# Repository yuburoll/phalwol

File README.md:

# phalwol
Row staggered 60% keyboard with reversible PCB, inspired by [Hatsukey70](https://scrapbox.io/Hatsukey/)

Hatsuki means August in Japanese, and phalwol means August in Korean. This keyboard layout is an hommage to Hatsukey70, so I want to credit the original design by name.

This keyboard has additional Y/H/B keys which positioned between keyboards, and auxilary row at left outside. You may put the keycaps from numpad.

This keyboard has hotswap-only PCB.

phalwol can change layout to followings:

- Split left shift, to ISO shaped one.(2.25u to 1.25u/1u)

- Split right shift, to HHKB inspired shape.(2.75u to 1.75u/1u)

- Split outside thumb keys(2u to 1u/1u)

- Split backspace(2u to 1u/1u)

- Can use stepped caps lock

## Preparation

- 2x pro micro form factor dev board

- 2x phalwol PCB Boards, provided from the repo

- 1x printed case sets, 2 parts total, provided from the repo (for thicker case, use "buffed")

- 1x 1.5-1.6T keyboard plate sets, 2 parts total, provided from the repo

- 80x diodes, normally 1N4148

- 84x Kailh hotswap sockets (or compatibles)

- 16x M2x6 screws, flathead

- 2x PJ320A 1/8(3.5mm) TRRS connector (MJ-4PP-9 in other name)

- 2x 4x4x1.5mm surface mount tact switches (optional, for dev boards without reset button)

- 1x 1/8(3.5mm) TRRS cable

- 1-6x PCB Mounted 2u Keyboard Stabilizers, normally 6

- 73-78x MX Keyswitches, normally 73

- 8x 10mm bumpon stickers

- A set of Keycaps, Full-size layout, ANSI preferred.

## Differences between case variations

|Original|Buffed|Frame|
|:---:|:---:|:---:|
||||

(Frame case are lightest option for 3d print, but it is very brittle)

## Build Guides and Miscellaneous

[phalwol Build Guide](docs/buildGuide.md)

there's some notices before the build:

- You may solder all hotswaps before soldering the dev board.

- Assemble dev board with 2.5mm height pin headers on back side, assume that components side are faced up.

- Jump every jumpers on front side.

[Additional Tenting Stand](https://github.com/yuburoll/yubuGadgets/tree/main/phalilwolTentingStand)

Also take a look at the sibling, [ilwol](https://github.com/yuburoll/ilwol).

## Licenses

All codes are in MIT License.

Markdown documents and photos in docs/images folder are copyrighted, all rights reserved.

The case and layout design of Phalwol is licensed under CC BY-NC-SA 4.0 (Attribution-NonCommercial-ShareAlike) by default, with an additional limited permission for commercial use under the following conditions:

- You are an individual, not acting on behalf of any company or organization.
  
- Your revenue from a single batch of sales does not exceed $2,000.
  
- Your sales are occasional and limited in scope, not ongoing or continuous.

If you want to ask any, please contact the authors.

- me: yuburoll@gmail.com

- Murasaki, the author of original layout Hatsukey70: https://scrapbox.io/Hatsukey/%E4%BD%9C%E8%80%85%E9%80%A3%E7%B5%A1%E5%85%88

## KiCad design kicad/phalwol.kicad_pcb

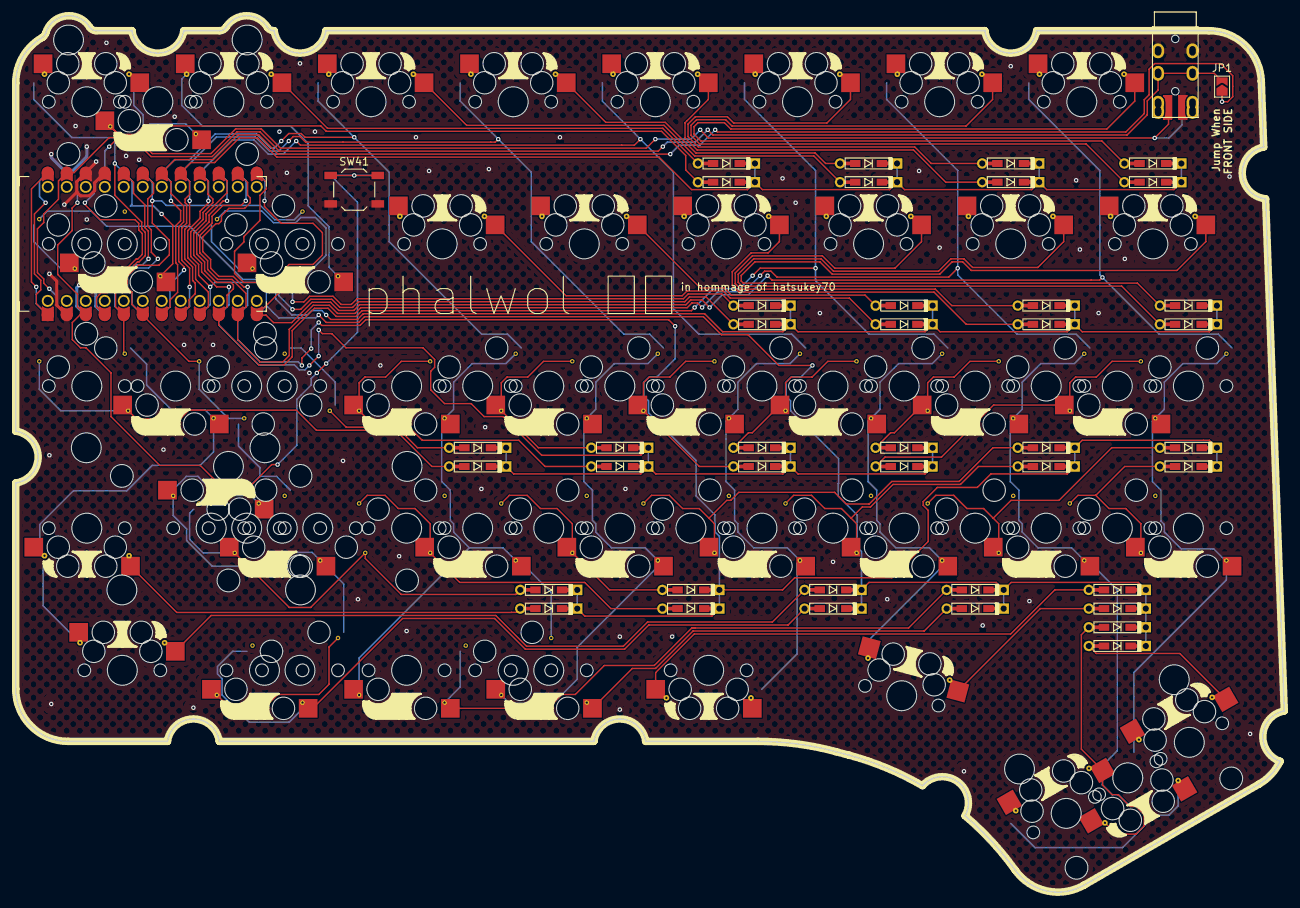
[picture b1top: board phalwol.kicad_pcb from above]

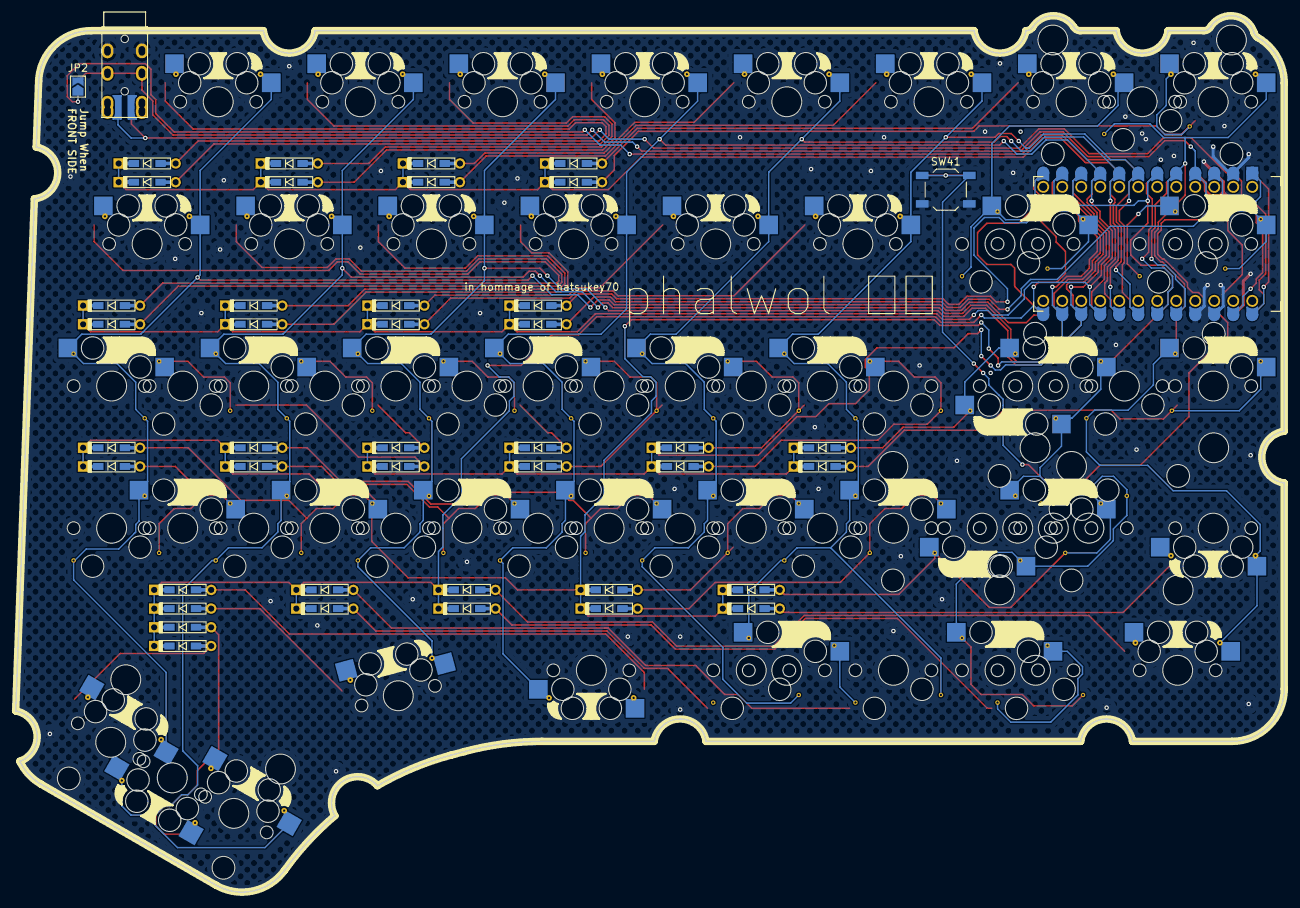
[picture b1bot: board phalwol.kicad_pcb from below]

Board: 2 copper layers, 169.6 x 117.1 mm, 108 parts (23 on the bottom side), 58 nets.

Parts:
D1, D2, D3, D4, D5, D6, D7, D8, D9, D10, D11, D12, D13, D14, D15, D16, D17, D18, D19, D20, D21, D22, D23, D24, D25, D26, D27, D28, D29, D30, D31, D32, D33, D34, D35, D36, D37, D38, D39, D40: D; Diode_TH_SMD_REVERSIBLE
J1: AudioJack4; TRRS-PJ-320A-ReversiblePad
JP1, JP2: SolderJumper_2_Open; SolderJumper-2_P1.3mm_Open_TrianglePad1.0x1.5mm
SW1, SW9, SW9#2, SW10, SW10#2, SW17, SW17#2, SW18, SW19, SW19#2, SW20, SW20#2, SW21, SW21#2, SW22, SW22#2, SW23, SW23#2, SW24, SW24#2, SW26, SW26#2, SW26#3, SW26#4, SW27, SW27#2, SW28, SW28#2, SW29, SW29#2, SW30, SW30#2, SW31, SW31#2, SW32, SW32#2, SW34, SW34#2, SW35, SW35#2, SW36: SW_Push; MX_HotswapOneside_Via_Guided
SW1#2, SW2, SW3, SW4, SW5, SW6, SW7, SW8, SW11, SW12, SW13, SW14, SW15, SW16, SW25, SW33, SW37, SW38, SW39, SW39#2, SW40: SW_Push; MX_Hotswap_FootprintPropertyFix_Guided
SW41, SW41#2: SW_Push; SW_SPST_TL3342
U1: ProMicro; ProMicro_ReveribleThru_ComponentUp_OuterPad

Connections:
COL1: SW1.1, SW1#2.1, SW9.1, SW9#2.1, SW17.1, SW17#2.1, SW25.1, SW33.1, U1.20 (F4/A3)
COL2: SW2.1, SW10.1, SW10#2.1, SW18.1, SW26.1, SW26#2.1, SW26#3.1, SW26#4.1, SW34.2, SW34#2.1, U1.19 (F5/A2)
COL3: SW3.1, SW11.1, SW19.1, SW19#2.1, SW27.1, SW27#2.1, SW35.2, SW35#2.1, U1.18 (F6/A1)
COL4: SW4.1, SW12.1, SW20.1, SW20#2.1, SW28.1, SW28#2.1, SW36.2, U1.17 (F7/A0)
COL5: SW5.1, SW13.1, SW21.1, SW21#2.1, SW29.1, SW29#2.1, SW37.1, U1.16 (B1/15)
COL6: SW6.1, SW14.1, SW22.1, SW22#2.1, SW30.1, SW30#2.1, SW38.1, U1.15 (B3/14)
COL7: SW7.1, SW15.1, SW23.1, SW23#2.1, SW31.1, SW31#2.1, SW39.1, SW39#2.1, U1.14 (B2/16)
COL8: SW8.1, SW16.1, SW24.1, SW24#2.1, SW32.1, SW32#2.1, SW40.1, U1.13 (B6/10)
GND: J1.R2, J1.S, JP2.2 (B), SW41.2, SW41#2.2, U1.3 (GND), U1.4 (GND), U1.23 (GND)
HAND: JP1.1 (A), JP2.1 (A), U1.7 (4/D4)
unnamed: D1.2 (A), SW1.2, SW1#2.2
unnamed: D2.2 (A), SW2.2
unnamed: D3.2 (A), SW3.2
unnamed: D4.2 (A), SW4.2
unnamed: D5.2 (A), SW5.2
unnamed: D6.2 (A), SW6.2
unnamed: D7.2 (A), SW7.2
unnamed: D8.2 (A), SW8.2
unnamed: D9.2 (A), SW9.2, SW9#2.2
unnamed: D10.2 (A), SW10.2, SW10#2.2
unnamed: D11.2 (A), SW11.2
unnamed: D12.2 (A), SW12.2
unnamed: D13.2 (A), SW13.2
unnamed: D14.2 (A), SW14.2
unnamed: D15.2 (A), SW15.2
unnamed: D16.2 (A), SW16.2
unnamed: D17.2 (A), SW17.2, SW17#2.2
unnamed: D18.2 (A), SW18.2
unnamed: D19.2 (A), SW19.2, SW19#2.2
unnamed: D20.2 (A), SW20.2, SW20#2.2
unnamed: D21.2 (A), SW21.2, SW21#2.2
unnamed: D22.2 (A), SW22.2, SW22#2.2
unnamed: D23.2 (A), SW23.2, SW23#2.2
unnamed: D24.2 (A), SW24.2, SW24#2.2
unnamed: D25.2 (A), SW25.2
unnamed: D26.2 (A), SW26.2, SW26#2.2, SW26#3.2, SW26#4.2
unnamed: D27.2 (A), SW27.2, SW27#2.2
unnamed: D28.2 (A), SW28.2, SW28#2.2
unnamed: D29.2 (A), SW29.2, SW29#2.2
unnamed: D30.2 (A), SW30.2, SW30#2.2
unnamed: D31.2 (A), SW31.2, SW31#2.2
unnamed: D32.2 (A), SW32.2, SW32#2.2
unnamed: D33.2 (A), SW33.2
unnamed: D34.2 (A), SW34.1, SW34#2.2
unnamed: D35.2 (A), SW35.1, SW35#2.2
unnamed: D36.2 (A), SW36.1
unnamed: D37.2 (A), SW37.2
unnamed: D38.2 (A), SW38.2
unnamed: D39.2 (A), SW39.2, SW39#2.2
unnamed: D40.2 (A), SW40.2
ROW1: D1.1 (K), D2.1 (K), D3.1 (K), D4.1 (K), D5.1 (K), D6.1 (K), D7.1 (K), D8.1 (K), U1.8 (5/C6)
ROW2: D9.1 (K), D10.1 (K), D11.1 (K), D12.1 (K), D13.1 (K), D14.1 (K), D15.1 (K), D16.1 (K), U1.9 (6/D7)
ROW3: D17.1 (K), D18.1 (K), D19.1 (K), D20.1 (K), D21.1 (K), D22.1 (K), D23.1 (K), D24.1 (K), U1.10 (7/E6)
ROW4: D25.1 (K), D26.1 (K), D27.1 (K), D28.1 (K), D29.1 (K), D30.1 (K), D31.1 (K), D32.1 (K), U1.11 (8/B4)
ROW5: D33.1 (K), D34.1 (K), D35.1 (K), D36.1 (K), D37.1 (K), D38.1 (K), D39.1 (K), D40.1 (K), U1.12 (9/B5)
RST: SW41.1, SW41#2.1, U1.22 (RST)
SERIAL: J1.T, U1.2 (RX1/D2)
VCC: J1.R1, JP1.2 (B), U1.21 (VCC)

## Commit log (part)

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2026-05-16 phalwol kicad upload
2026-05-16 update pcb and schema
2026-05-16 connect schema and pcb
2026-05-17 update pcb
2026-05-19 finished wiring
2026-05-19 hotfix wiring
2026-05-21 fix proper hole position
2026-05-22 add phalwol board art
2026-05-22 polish pcb
2026-05-29 create gerber
2026-06-02 change modifier cluster to fixed one
2026-06-05 gerber update
2026-06-05 edit hole size for jack
2026-06-05 edit case for stabilizer collide
2026-06-05 minor hole changement
2026-06-05 edit pcb for proper design'
2026-06-11 change hole offset
2026-06-13 upload firmward and json
2026-06-13 upload images
2026-06-13 case upload
2026-06-13 add buffcase for phalwol
2026-06-13 add 3mf and fix non-manifold geo
2026-06-16 add build guide(draft from pisic)
2026-06-16 finish build guide
2026-06-18 change fillet of case for cnc
2026-06-18 add plate stp file
2026-06-19 add promicro firmware and vial example
2026-06-19 add image check for case
2026-06-20 change images to new one
